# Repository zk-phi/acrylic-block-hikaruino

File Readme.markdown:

# Acrylic block hikaruino

pixiv FACTORY のアクリルブロックを光らせるのにちょうどいいかもしれない大きさの AVR ボードです。

前面にフルカラー LED が５個付いています。

部品実装イメージ

https://booth.pm/ja/items/1530537

内輪ネタです。

## 注意

動作未確認です。

基板にプリントされているテキスト通りに部品を揃えて組み立てれば、 `dfu-programmer` とかでプログラムを書き込めると思います。多分。

## ライセンス

以下のどちらかを満たす限り自由に再配布、製造販売できる

- らりょすアイコンを削除し、それ以外の改変を加えない
- らりょすアイコン、作者名表記をともに削除した上で自明でない改良を加え、改変元と改変箇所をわかりやすく表示する

ただしあなたがらりょすの場合はアイコンを削除しなくて良い

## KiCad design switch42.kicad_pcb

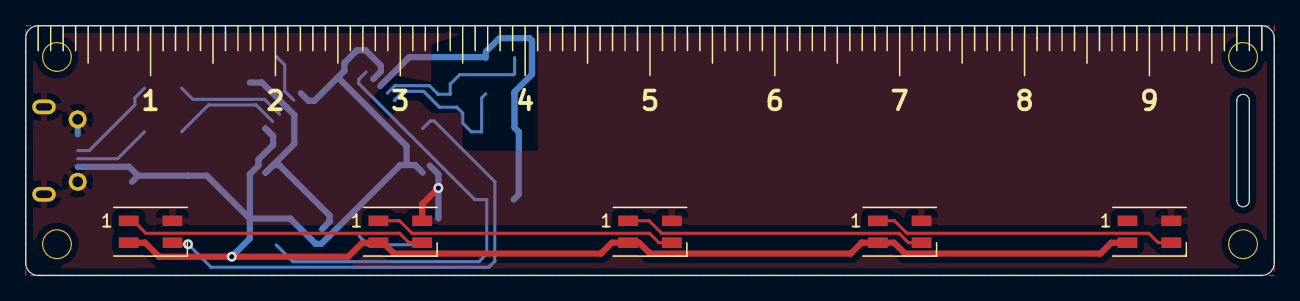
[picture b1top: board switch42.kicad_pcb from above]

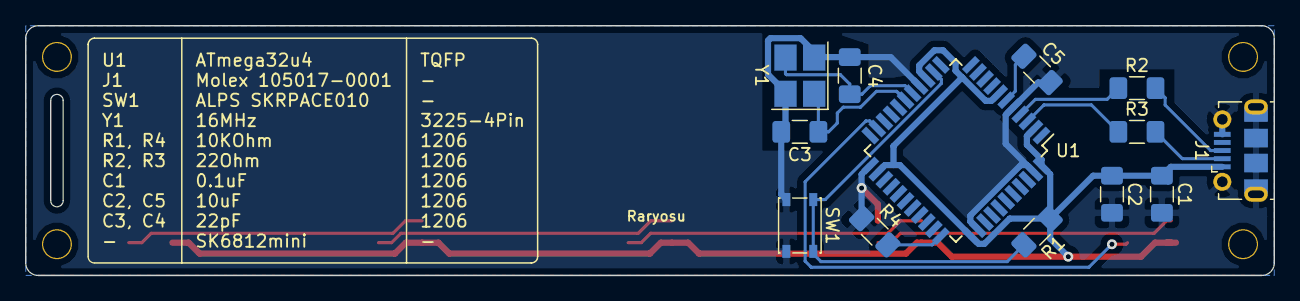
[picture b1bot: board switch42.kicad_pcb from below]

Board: 2 copper layers, 100.0 x 20.0 mm, 22 parts (13 on the bottom side), 16 nets.

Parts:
C1, C2, C5: C; C_1206_3216Metric_Pad1.42x1.75mm_HandSolder
C3, C4: C_Small; C_1206_3216Metric_Pad1.42x1.75mm_HandSolder
D1, D2, D3, D4, D5: SK6812MINI; LED_SK6812MINI_PLCC4_3.5x3.5mm_P1.75mm
J1: USB_B_Micro; USB_Micro-B_Molex-105017-0001
R1, R2, R3, R4: R; R_1206_3216Metric_Pad1.42x1.75mm_HandSolder
Ref**: Val**; M2_SCREW_HOLE
Ref**#2, Ref**#3, Ref**#4: Val**; M2_SCREW_HOLE
SW1: SW_PUSH; SW_SPST_PTS810
U1: ATmega32U4-AU; TQFP-44_10x10mm_P0.8mm
Y1: Crystal_GND24; Crystal_SMD_3225-4Pin_3.2x2.5mm_HandSoldering

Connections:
D+: R2.1, U1.4
D-: R3.1, U1.3
GND: C1.2, C2.2, C3.2, C4.2, C5.2, D1.4, D2.4, D3.4, D4.4, D5.4, J1.5, J1.6, R4.1, SW1.2, U1.5, U1.15, U1.23, U1.35, U1.43, Y1.2, Y1.4
LED: D1.3, U1.21
unnamed: C5.1, U1.6
unnamed: D1.1, D2.3
unnamed: D2.1, D3.3
unnamed: D3.1, D4.3
unnamed: D4.1, D5.3
unnamed: J1.2, R3.2
unnamed: J1.3, R2.2
unnamed: R4.2, U1.33
RESET: R1.2, SW1.1, U1.13
UVCC: C1.1, C2.1, D1.2, D2.2, D3.2, D4.2, D5.2, J1.1, R1.1, U1.2, U1.7, U1.14, U1.24, U1.34, U1.44
XTAL1: C3.1, U1.17, Y1.1
XTAL2: C4.1, U1.16, Y1.3

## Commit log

2019-09-06 PCB v0.1
2019-09-06 Add gerber
2019-09-06 Add Readme
2019-09-06 Rename gerber dir
2019-09-06 Add images
